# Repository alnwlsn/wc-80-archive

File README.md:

# The WC-80 (archive)

My homebrew Z80 computer which is not exactly a TRS-80 Model 1 clone. Archive from 2020-2023.

## Background
Some time ago when I was in college (not that long ago, mind you, it was like 2018), I found a TRS-80 Model 1. It was the first (non-IBM PC) retrocomputer I had ever got my hands on, and in my book, is absolutely legendary, for reasons I'll have to get into some other time. What's important is that what I got was *only* the keyboard, so no power supply, no cables, no display. The first thing I tried to do with it was cobble up a power supply, and wire up an adapter so I could plug the machine into a regular TV's composite video. I powered it on. It was a working unit. 

What you get with just the base Model 1 "keyboard" is:
- Z80 CPU @ 1.77 MHz
- ROM with Level II (microsoft) BASIC
- 16K of RAM
- video output
    - "almost" NTSC / RS170 (black and white only)
    - 64 columns x 16 rows, 6x12 px character resolution, fixed character set
- cassette interface
- the keyboard itself

That's  pretty limiting if you want to do stuff(tm) with the machine. In particular, the cassette interface is a real bottleneck, taking minutes on end to load things, and it's the only way to do so besides typing it in. People thought so too in the TRS-80's heyday, so the platform evolved to have floppy disks, more memory, various operating systems, a serial port, maybe even a hard drive. These were provided by a box that plugs into the TRS-80's keyboard called the 'Expansion Interface (EI)' I did not an Expansion Interface, and they were rare and expensive on Ebay. But, the TRS-80 is old enough that it is made mostly out of standard 74 logic ICs, rather than custom chips like the C64 or later machines have, and all the schematics are right there in the manual. Having more time than any other resource back then, I thought to myself "how hard can it be?"

Following the schematics, this is what led me to create my [hand-wired Expansion Interface unit](https://alnwlsn.com/projectrepository/index.php?title=TRS-80_Model_1_-_Wilson_Expansion_Interface) and had me boot my TRS-80 from a floppy disk for possibly the first time in its life. That was not quite built as stock though:
- SRAM for extra RAM instead of DRAMs
    - why not, RAM is cheap here in the future
    - 128K ram used, in 4 swappable banks of 32K
        - just because I can, haven't done much with this
- Arduino with 1K dual port RAM put in 'hole' in TRS-80 memory map at 0x3000
    - easy and quick way to get data from modern laptop to TRS-80 RAM
- 'equivalent' logic gates, not exact chips used in EI (based on what chips I happened to have or get easily)

The hand built unit had obvious problems though:
- tedious soldering assembly
- unreliable "stacked pin header" interconnects
- not very modular, hard to add more hardware
- fragile

I then started this project to clean up the hand built unit into some real PCBs, which would go into a backplane. If I wanted to add more hardware, I could just make another card. After building most of the EI, I realized that there wasn't all that much to the rest of the computer, so I built modules for that too. Thus, the WC-80 (W Cube Z80) was born.

It's a bit like a Model 1, with some Model III (more IO on the IO ports) and Model 4 (some peripherals like the video ram and keyboard can be moved around in the memory map, and there are multiple banks of memory). The main difference is that most of the hardware options are software controlled, so it needs to boot a rom that can initialize all the hardware, then load the TRS-80 ROMs and jump to the beginning of it.

As the system took shape, I thought I might install it into a case, and make a portable machine, but soon obtained a good number of real TRS-80 machines to work on instead. I haven't touched the WC-80 much since around 2022, which means I've forgotten most of whatever I was doing on it. Still, it's probably more useful published here as incomplete than just sitting on my hard drive. When I pick up this project again, I'll probably continue in a new repo, which will be linked here if it exists.

## General guidelines:
- 100x100mm typical board size
    - this is the cheap "loss leader" size offered by PCBWay and JLC. A board twice this area costs more than double the price.
- where possible, SMD SOIC packages
    - much more compact than DIP, but still easily solderable by hand with an iron
        - plus, you don't have to flip the board over
- 2 layer boards (cheapest)
- 0.2mm track width for data signals
    - fits between SOIC pads
- 74HCT (CMOS w/ TTL level inputs) over HC or LS parts, where possible
- autorouted (w/ some manual routing) with [TopoR](https://en.wikipedia.org/wiki/TopoR)
    - usually get my fill of manually routing boards at work
- designed around whatever ICs I can get for cheap
- fit as much stuff as I can onto each board
    - I paid for the whole board, I'm gonna use the whole board

## Boards
### Backplane

- 40-pin interconnect is derived from the 40-pin card edge on the back of the TRS-80 Model 1, though a few pins are different, so it can't be plugged in directly.
- 8 pin connectors on either side are for power and misc. signals.
- [next revision](boards/backplane2/new/) is just a straight interconnect, which is how it probably should be.
- [this version shown](boards/backplane/) has named nets, and the power rails and GNDs are connected together on the backplane.

### CPU board

- Z80 CPU
- memory map divided into 4x 16k slots, into which any 1 of 32 pages of RAM or 1 of any 32 pages of Flash ROM can be installed. 
    - bank selection by IO port
    - whole memory space is filled, but there is an INUSE pin on the backplane by which other boards can signal the CPU board that they want to use the memory space currently being accessed, in which case on-board memory will be disabled
- software selectable clock rate from 1.77MHz to 8MHz
    - CPU clock provided by a 16MHz clock feeding a counter chip which can count from 2 to 9. 16/9 happens to be pretty close to the 1.77MHz of the model 1. You also get more traditional clock rates of 2, 4 and 8Mhz.
- added the Model 1's cassette interface
    - can read and write TRS-80 Model 1 Level II tapes when running Level II ROMs
    - it can even load tapes played back at 4x speed in 8Mhz mode, seems to work just fine
    - includes reed relay for cassette remote switch
- battery backed RAM with integral RTC via [DS1315 Phantom Time chip](https://www.analog.com/en/products/ds1315.html)
    -   to get and set the RTC, you write a sequential series of special bytes to the RAM and the next byte written will come from the RTC
        - execution must be done either in a ROM or from external RAM, since you can't be both read the instructions and write the special sequence while being on the internal RAM
        - probably get rid of this in the next version, the Arduino board has the same thing already
- [I think this is the current version of the CPU](boards/cpu/cpu-rev2/)

### Keyboard

- key switches wired per TRS-80 key matrix
- NMI and Reset keys broken out on board
- some extra keys for which there is room on the matrix but normally no switch there (Control key, etc) have been added 
- memory mapped, but relocatable from the default 3800 address, like a model 4
    - only uses 256 addresses, not the minimally decoded 1K the Model 1 has
- 8 leds
- a fairly standard mechanical keyboard build otherwise
- keycaps are [custom labeled](keyboard-labels/) using the [lasered toner method](https://www.youtube.com/watch?v=_V5DmHmCMaU)
- this was supposed to be a simple PCB mounted switch design, but the switches I got ended up being plate mounted. I had to reconfigure my CNC machine to be a 3D printer, as I did not have one large enough to print a full-sized backplate at the time.

### Old CPU

- [despite being called 'cpu5' and the new one being 'cpu2', this is the older one](boards/cpu/cpu5/)
- same as the current CPU board, only using DIP chips and having a HP Dl1414 4-character LED display instead of the cassette interface. This display is usually not visible, so I got rid of it.

```alnwlsn-ssg
title: The WC-80 (archive)
subtitle: homebrew TRS-80 I made one time
date: 2025-07-16
labels: retrocomputing, trs80
```

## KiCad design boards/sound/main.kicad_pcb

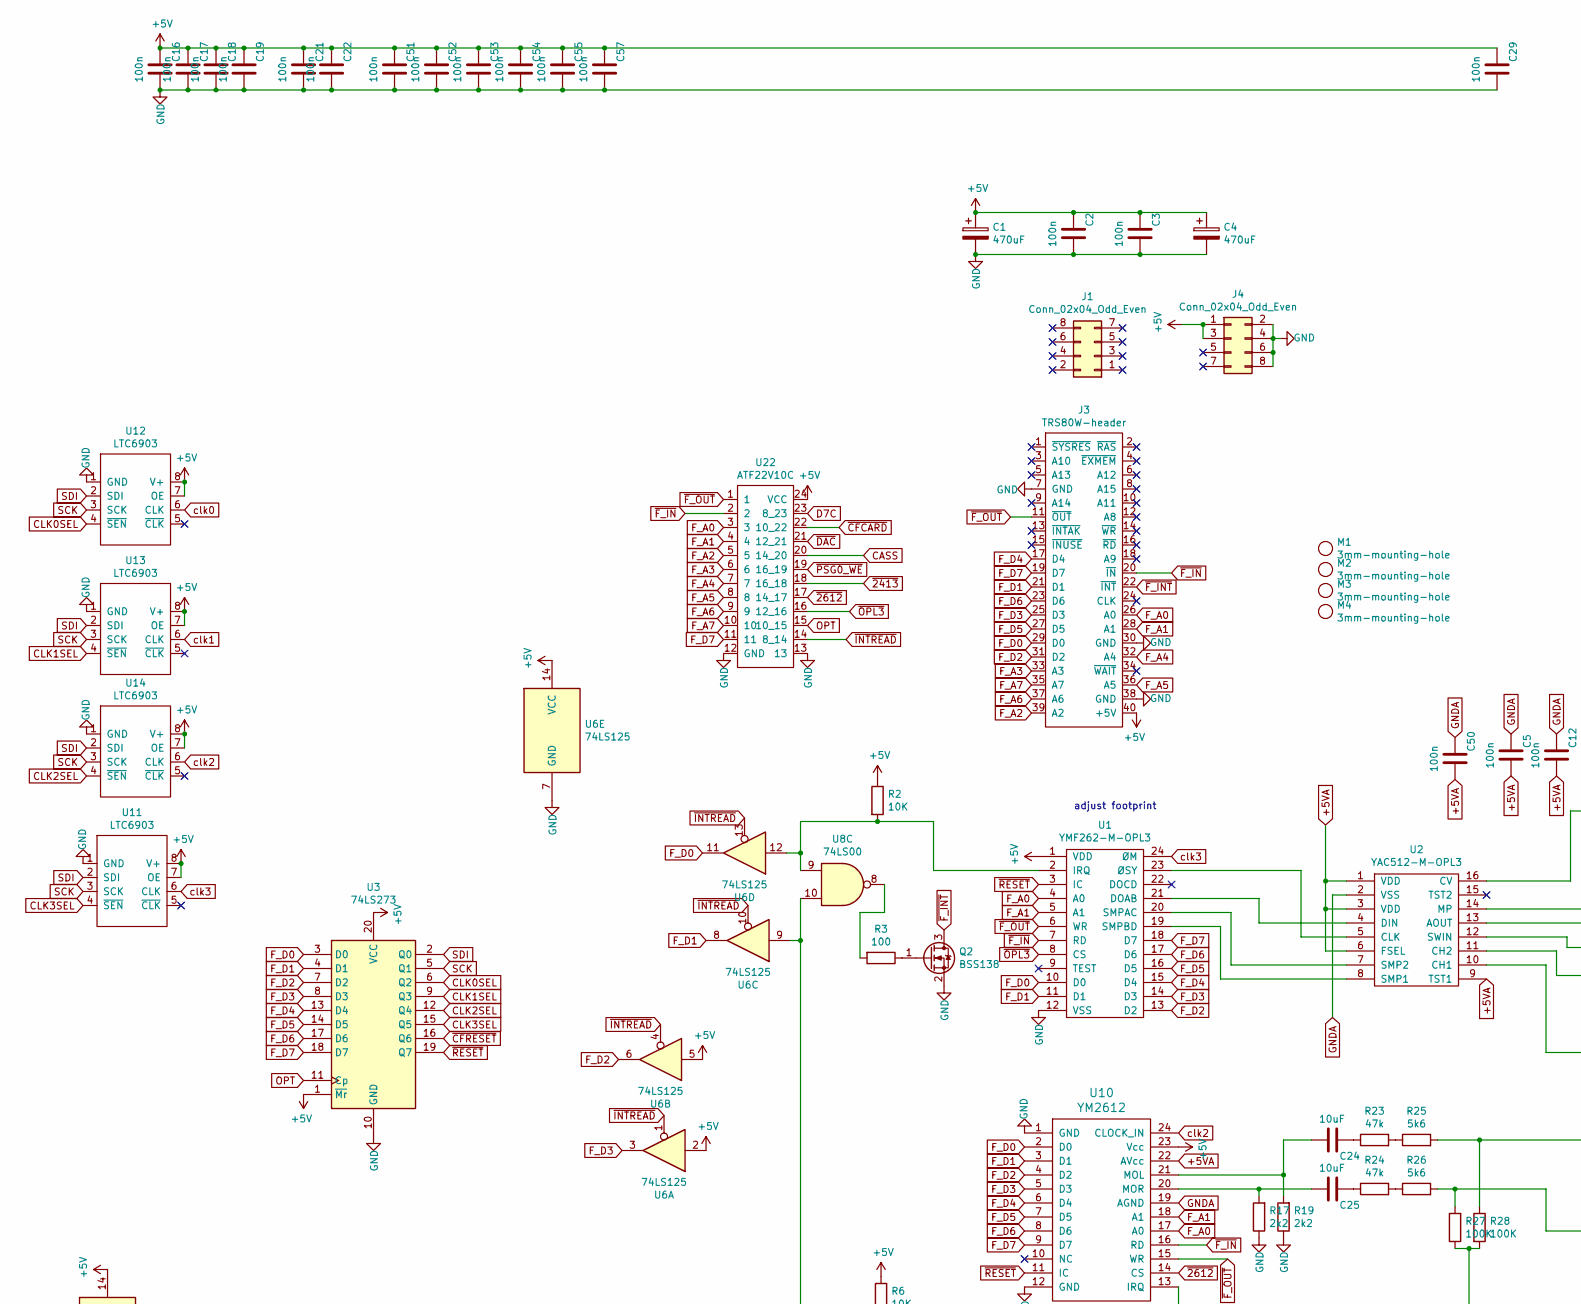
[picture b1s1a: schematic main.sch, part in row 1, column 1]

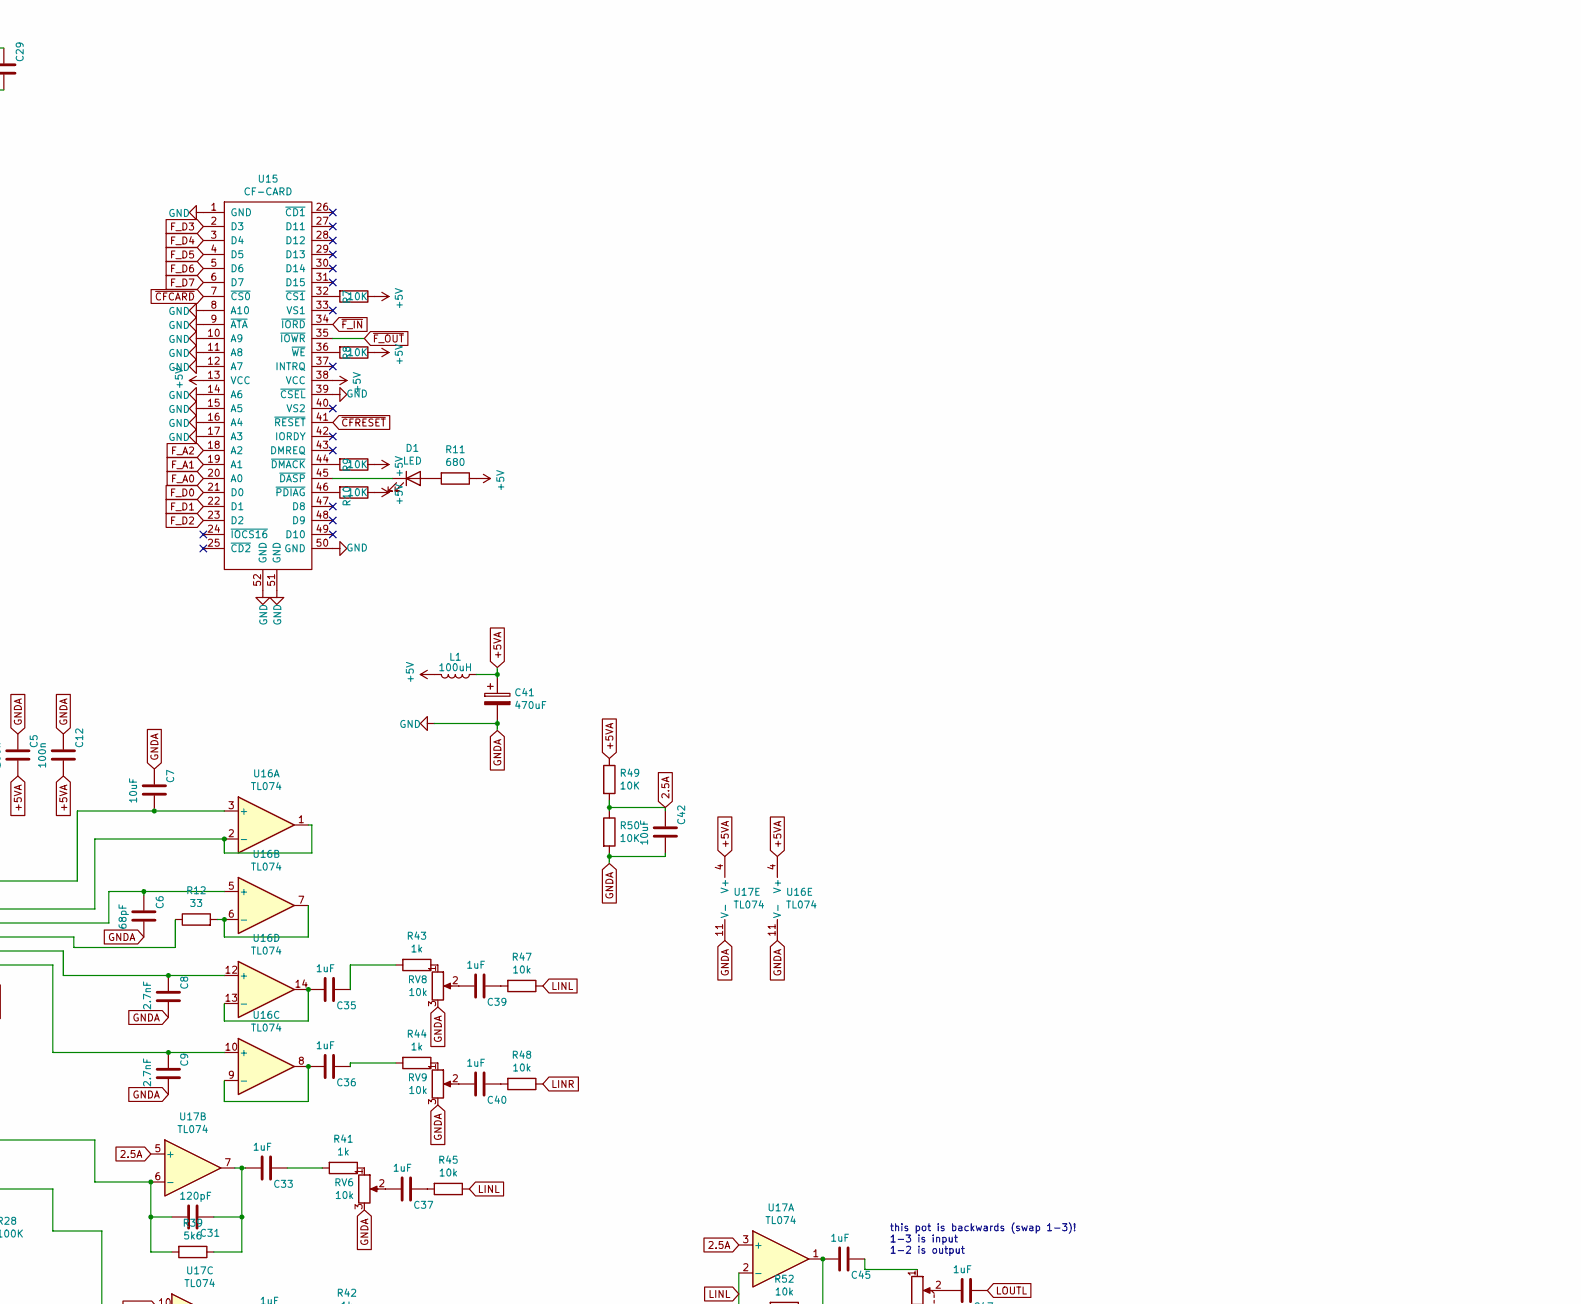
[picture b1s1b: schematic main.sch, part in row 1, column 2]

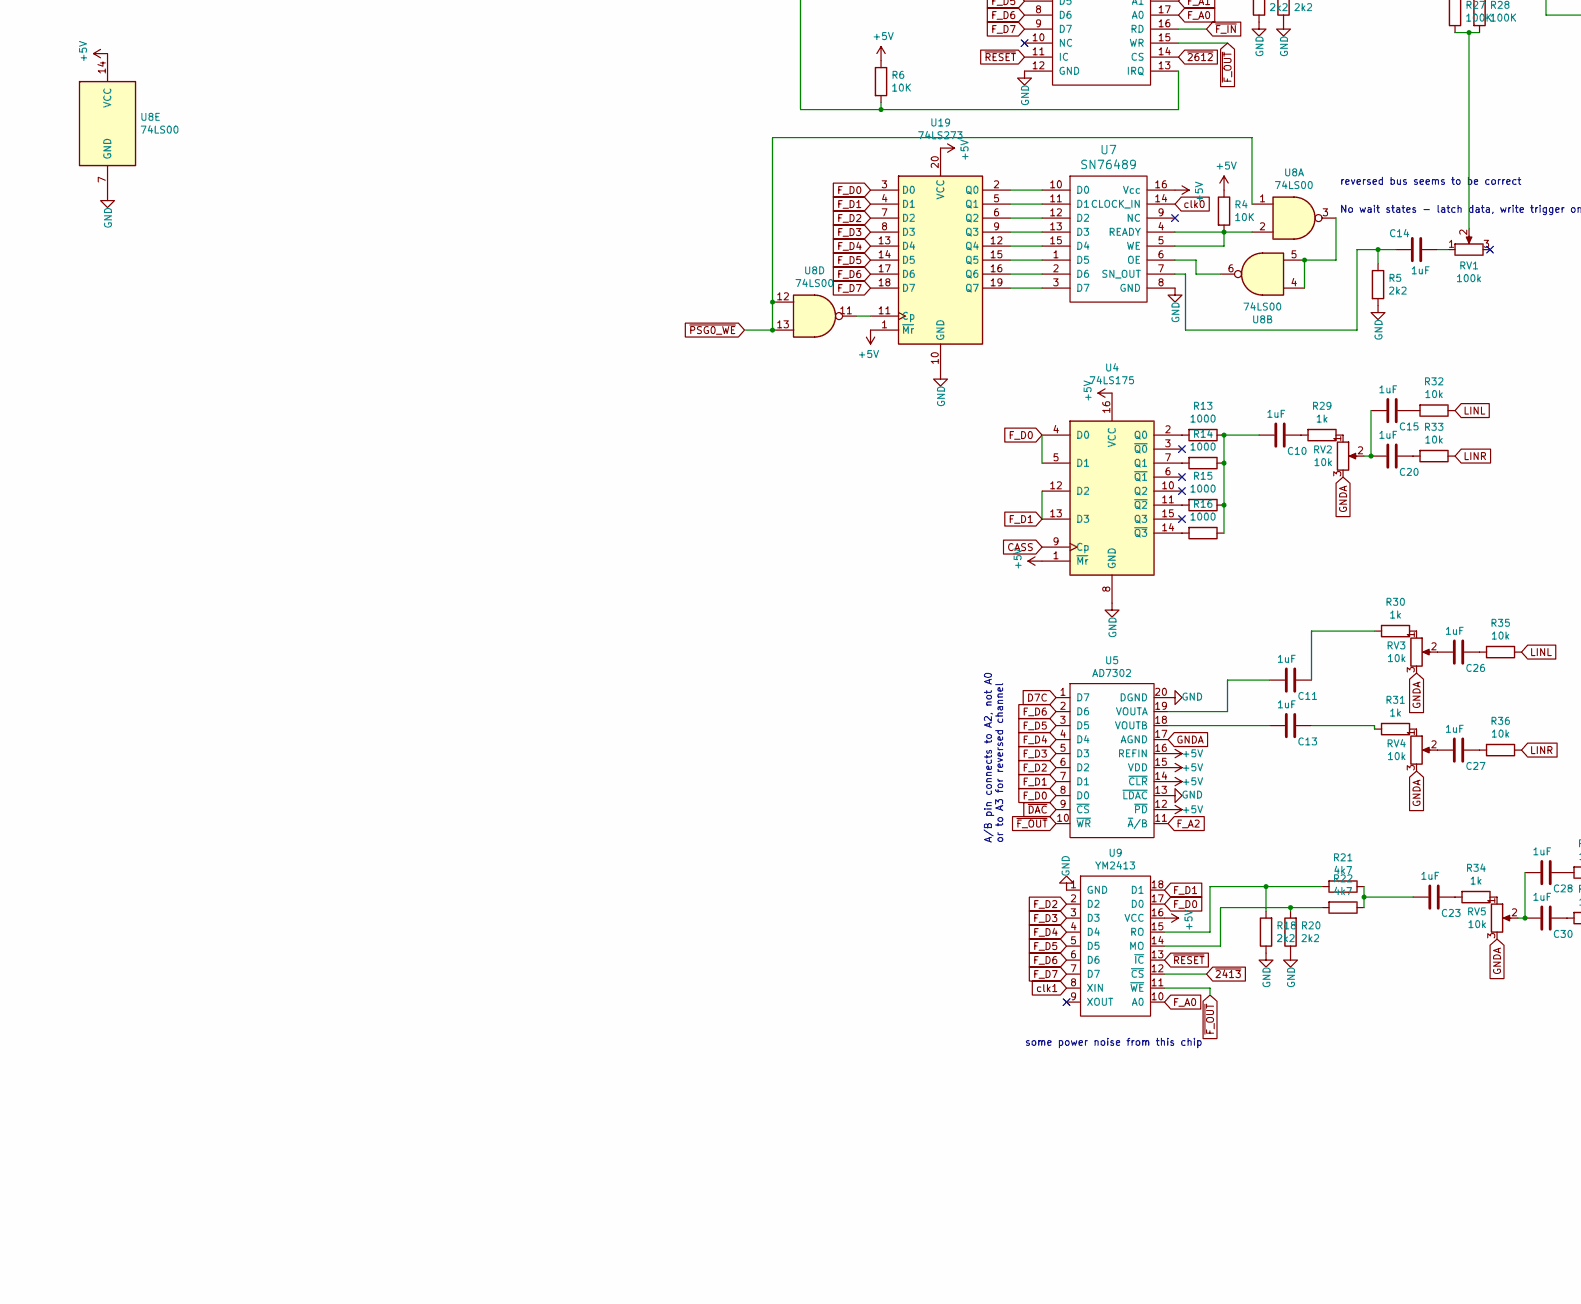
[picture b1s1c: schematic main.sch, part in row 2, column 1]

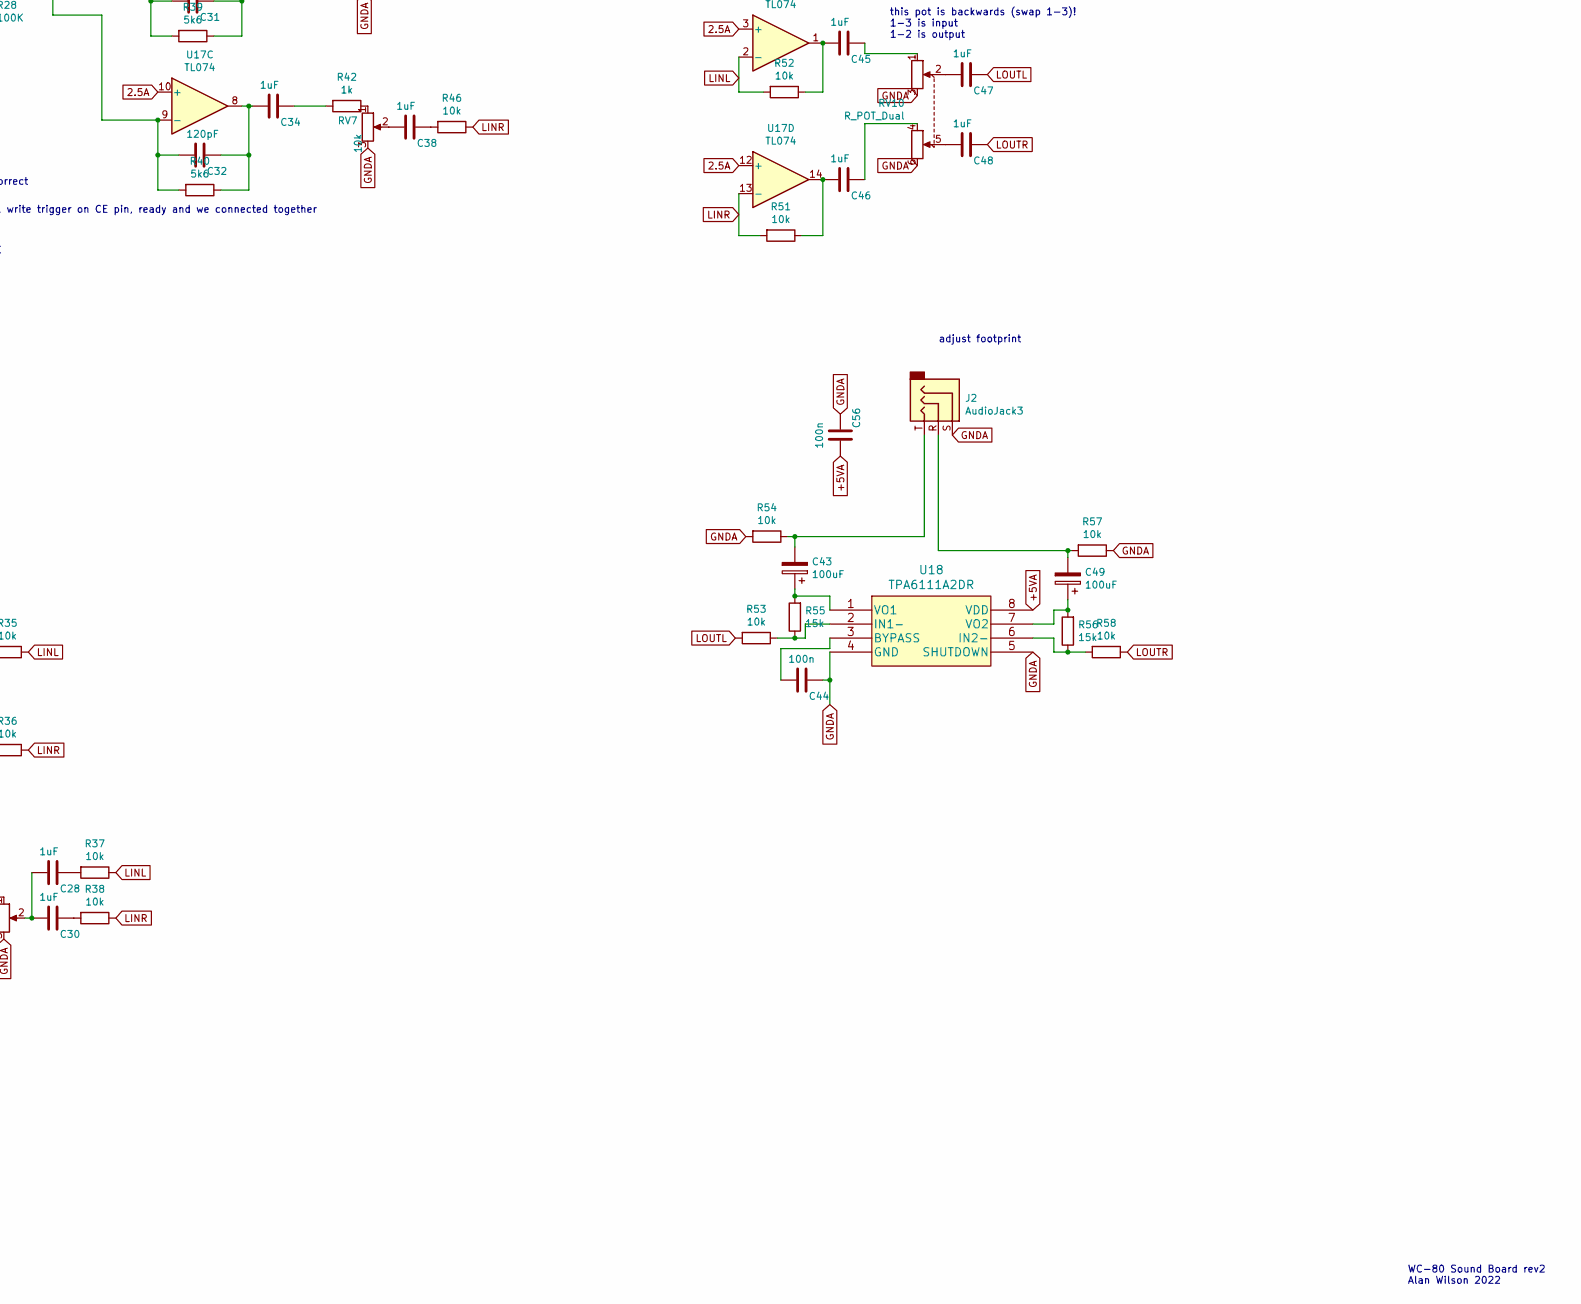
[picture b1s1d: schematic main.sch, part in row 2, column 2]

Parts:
C1, C4, C41: 470uF; CP_Radial_D8.0mm_P3.50mm
C2, C3, C5, C12, C16, C17, C18, C19, C21, C22, C29, C44, C50, C51, C52, C53, C54, C55, C56, C57: 100n; C_0805_2012Metric
C6: 68pF; C_0805_2012Metric
C7, C24, C25, C42: 10uF; C_0805_2012Metric
C8, C9: 2.7nF; C_0805_2012Metric
C10, C11, C13, C14, C15, C20, C23, C26, C27, C28, C30, C33, C34, C35, C36, C37, C38, C39, C40, C45, C46, C47, C48: 1uF; C_0805_2012Metric
C31, C32: 120pF; C_0805_2012Metric
C43, C49: 100uF; CP_Elec_6.3x5.4
D1: LED; LED_D3.0mm
J1, J4: Conn_02x04_Odd_Even; PinHeader_2x04_P2.54mm_Vertical
J2: AudioJack3; SWITCHCRAFT_35RAPC4BHN2
J3: TRS80W-header; PinHeader_2x20_P2.54mm_Vertical
L1: 100uH; SWPA5040S
M1, M2, M3, M4: 3mm-mounting-hole; MountingHole_3.2mm_M3_DIN965
Q2: BSS138; SOT-23
R2, R4, R6, R7, R8, R9, R10, R49, R50: 10K; R_0805_2012Metric
R3: 100; R_0805_2012Metric
R5, R17, R18, R19, R20: 2k2; R_0805_2012Metric
R11: 680; R_0805_2012Metric
R12: 33; R_0805_2012Metric
R13, R14, R15, R16: 1000; R_0805_2012Metric
R21, R22: 4k7; R_0805_2012Metric
R23, R24: 47k; R_0805_2012Metric
R25, R26, R39, R40: 5k6; R_0805_2012Metric
R27, R28: 100K; R_0805_2012Metric
R29, R30, R31, R34, R41, R42, R43, R44: 1k; R_0805_2012Metric
R32, R33, R35, R36, R37, R38, R45, R46, R47, R48, R51, R52, R53, R54, R57, R58: 10k; R_0805_2012Metric
R55, R56: 15k; R_0805_2012Metric
RV1: 100k; 3362P-1-103LF
RV2, RV3, RV4, RV5, RV6, RV7, RV8, RV9: 10k; 3362P-1-103LF
RV10: R_POT_Dual; Potentiometer_Alps_RK097_Dual_Horizontal
U1: YMF262-M-OPL3; SOIC-24W_7.5x15.4mm_P1.27mm
U2: YAC512-M-OPL3; SOIC-16W_5.3x10.2mm_P1.27mm
U3, U19: 74LS273; SO-20_5.3x12.6mm_P1.27mm
U4: 74LS175; SOIC-16_3.9x9.9mm_P1.27mm
U5: AD7302; SOIC-20W_7.5x12.8mm_P1.27mm
U6: 74LS125; SOIC-14_3.9x8.7mm_P1.27mm
U7: SN76489; DIP-16_W7.62mm_Socket
U8: 74LS00; SOIC-14_3.9x8.7mm_P1.27mm
U9: YM2413; DIP-18_W7.62mm_Socket
U10: YM2612; DIP-24_W15.24mm_Socket
U11, U12, U13, U14: LTC6903; MSOP-8_3x3mm_P0.65mm
U15: CF-CARD; UMAX CFH-L3C1LBL01MN0
U16: TL074
U17: TL074; SOIC-14_3.9x8.7mm_P1.27mm
U18: TPA6111A2DR; SOIC-8_3.9x4.9mm_P1.27mm
U22: ATF22V10C; DIP-24_W7.62mm_Socket

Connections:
2.5A: C42.1, R49.2, R50.1, U17.3 (+), U17.5 (+), U17.10 (+), U17.12 (+)
+5V: C1.1, C2.1, C3.1, C4.1, C16.1, C17.1, C18.1, C19.1, C21.1, C22.1, C29.1, C51.1, C52.1, C53.1, C54.1, C55.1, C57.1, J3.40 (+5V), J4.1, J4.3, L1.2, R2.1, R4.1, R6.1, R7.1, R8.1, R9.1, R10.1, R11.1, U1.1 (VDD), U3.1 (~Mr), U3.20 (VCC), U4.1 (~Mr), U4.16 (VCC), U5.12 (~PD~), U5.14 (~CLR~), U5.15 (VDD), U5.16 (REFIN), U6.2, U6.5, U6.14 (VCC), U7.16 (Vcc), U8.14 (VCC), U9.16 (VCC), U10.23 (Vcc), U11.7 (OE), U11.8 (V+), U12.7 (OE), U12.8 (V+), U13.7 (OE), U13.8 (V+), U14.7 (OE), U14.8 (V+), U15.13 (VCC), U15.38 (VCC), U19.1 (~Mr), U19.20 (VCC), U22.24 (VCC)
+5VA: C5.2, C12.2, C41.1, C50.2, C56.2, L1.1, R49.1, U2.1 (VDD), U2.3 (VDD), U2.6 (FSEL), U2.9 (TST1), U10.22 (AVcc), U16.4 (V+), U17.4 (V+), U18.8 (VDD)
CASS: U4.9 (Cp), U22.20 (14_20)
CLK0SEL: U3.6 (Q2), U12.4 (~SEN~)
CLK1SEL: U3.9 (Q3), U13.4 (~SEN~)
CLK2SEL: U3.12 (Q4), U14.4 (~SEN~)
CLK3SEL: U3.15 (Q5), U11.4 (~SEN~)
D7C: U5.1 (D7), U22.23 (8_23)
F_A1: J3.28 (A1), U1.5 (A1), U10.18 (A1), U15.19 (A1), U22.4
F_A3: J3.33 (A3), U22.6
F_A4: J3.32 (A4), U22.7
F_A5: J3.36 (A5), U22.8
F_A6: J3.37 (A6), U22.9
F_A7: J3.35 (A7), U22.10
F_D0: J3.29 (D0), U1.10 (D0), U3.3 (D0), U4.4 (D0), U4.5 (D1), U5.8 (D0), U6.11, U7.10 (D0), U9.17 (D0), U10.2 (D0), U15.21 (D0), U19.2 (Q0), U19.3 (D0)
F_D1: J3.21 (D1), U1.11 (D1), U3.4 (D1), U4.12 (D2), U4.13 (D3), U5.7 (D1), U6.8, U7.11 (D1), U9.18 (D1), U10.3 (D1), U15.22 (D1), U19.4 (D1), U19.5 (Q1)
F_D2: J3.31 (D2), U1.13 (D2), U3.7 (D2), U5.6 (D2), U6.6, U7.12 (D2), U9.2 (D2), U10.4 (D2), U15.23 (D2), U19.6 (Q2), U19.7 (D2)
F_D3: J3.25 (D3), U1.14 (D3), U3.8 (D3), U5.5 (D3), U6.3, U7.13 (D3), U9.3 (D3), U10.5 (D3), U15.2 (D3), U19.8 (D3), U19.9 (Q3)
F_D4: J3.17 (D4), U1.15 (D4), U3.13 (D4), U5.4 (D4), U7.15 (D4), U9.4 (D4), U10.6 (D4), U15.3 (D4), U19.12 (Q4), U19.13 (D4)
F_D5: J3.27 (D5), U1.16 (D5), U3.14 (D5), U5.3 (D5), U7.1 (D5), U9.5 (D5), U10.7 (D5), U15.4 (D5), U19.14 (D5), U19.15 (Q5)
F_D6: J3.23 (D6), U1.17 (D6), U3.17 (D6), U5.2 (D6), U7.2 (D6), U9.6 (D6), U10.8 (D6), U15.5 (D6), U19.16 (Q6), U19.17 (D6)
F_D7: J3.19 (D7), U1.18 (D7), U3.18 (D7), U7.3 (D7), U9.7 (D7), U10.9 (D7), U15.6 (D7), U19.18 (D7), U19.19 (Q7), U22.11
F_WAIT: J3.34 (~WAIT~); also elsewhere on the board
LINL: R32.1, R35.1, R37.1, R45.1, R47.1, R52.2, U17.2 (-)
LINR: R33.1, R36.1, R38.1, R46.1, R48.1, R51.2, U17.13 (-)
LOUTL: C47.1, R53.2
LOUTR: C48.1, R58.1
unnamed: C6.1, U2.13 (AOUT), U16.5 (+)
unnamed: C7.2, U2.16 (CV), U16.3 (+)
unnamed: C8.1, U2.11 (CH2), U16.12 (+)
unnamed: C9.1, U2.10 (CH1), U16.10 (+)
unnamed: C10.1, R29.2
unnamed: C10.2, R13.1, R14.1, R15.1, R16.1
unnamed: C11.1, R30.2
unnamed: C11.2, U5.19 (VOUTA)
unnamed: C13.1, R31.2
unnamed: C13.2, U5.18 (VOUTB)
unnamed: C14.1, R5.1, U7.7 (SN_OUT)
unnamed: C14.2, RV1.1
unnamed: C15.1, R32.2
unnamed: C15.2, C20.2, RV2.2
unnamed: C20.1, R33.2
unnamed: C23.1, R34.2
unnamed: C23.2, R21.1, R22.1
unnamed: C24.1, R23.1
unnamed: C24.2, R19.2, U10.21 (MOL)
unnamed: C25.1, R24.1
unnamed: C25.2, R17.2, U10.20 (MOR)
unnamed: C26.1, R35.2
unnamed: C26.2, RV3.2
unnamed: C27.1, R36.2
unnamed: C27.2, RV4.2
unnamed: C28.1, R37.2
unnamed: C28.2, C30.2, RV5.2
unnamed: C30.1, R38.2
unnamed: C31.1, C33.2, R39.1, U17.7
unnamed: C31.2, R25.2, R28.1, R39.2, U17.6 (-)
unnamed: C32.1, C34.2, R40.1, U17.8
unnamed: C32.2, R26.2, R27.2, R40.2, U17.9 (-)
unnamed: C33.1, R41.2
unnamed: C34.1, R42.2
unnamed: C35.1, R43.2
unnamed: C35.2, U16.13 (-), U16.14
unnamed: C36.1, R44.2
unnamed: C36.2, U16.8, U16.9 (-)
unnamed: C37.1, R45.2
unnamed: C37.2, RV6.2
unnamed: C38.1, R46.2
unnamed: C38.2, RV7.2
unnamed: C39.1, R47.2
unnamed: C39.2, RV8.2
unnamed: C40.1, R48.2
unnamed: C40.2, RV9.2
unnamed: C43.1, R55.2, U18.1 (VO1)
unnamed: C43.2, J2.T, R54.1
unnamed: C44.2, U18.3 (BYPASS)
unnamed: C45.1, RV10.1
unnamed: C45.2, R52.1, U17.1
unnamed: C46.1, RV10.4
unnamed: C46.2, R51.1, U17.14
unnamed: C47.2, RV10.2
unnamed: C48.2, RV10.5
unnamed: C49.1, R56.2, U18.7 (VO2)
unnamed: C49.2, J2.R, R57.2
unnamed: D1.1 (K), U15.45 (~DASP~)
unnamed: D1.2 (A), R11.2
unnamed: Q2.1 (G), R3.1
unnamed 115: U8.11, U19.11 (Cp); also elsewhere on the board
unnamed: R2.2, U1.2 (IRQ), U6.12, U8.9
unnamed: R3.2, U8.8
unnamed: R6.2, U6.9, U8.10, U10.13 (IRQ)
unnamed: R7.2, U15.32 (~CS1~)
unnamed: R8.2, U15.36 (~WE~)
unnamed: R9.2, U15.44 (~DMACK~)
unnamed: R10.2, U15.46 (~PDIAG~)
unnamed: R12.1, U2.12 (SWIN)
unnamed: R12.2, U16.6 (-), U16.7
unnamed: R13.2, U4.2 (Q0)
unnamed: R14.2, U4.7 (Q1)
unnamed: R15.2, U4.11 (~Q2)
unnamed: R16.2, U4.14 (~Q3)
unnamed: R18.2, R21.2, U9.15 (RO)
unnamed: R20.2, R22.2, U9.14 (MO)
unnamed: R23.2, R25.1
unnamed: R24.2, R26.1
unnamed: R27.1, R28.2, RV1.2
unnamed: R29.1, RV2.1
unnamed: R30.1, RV3.1
unnamed: R31.1, RV4.1
unnamed: R34.1, RV5.1
unnamed: R41.1, RV6.1
unnamed: R42.1, RV7.1
unnamed: R43.1, RV8.1
unnamed: R44.1, RV9.1
unnamed: R53.1, R55.1, U18.2 (IN1-)
unnamed: R56.1, R58.2, U18.6 (IN2-)
unnamed: U1.19 (SMPBD), U2.8 (SMP1)
unnamed: U1.20 (SMPAC), U2.7 (SMP2)
unnamed: U1.21 (DOAB), U2.4 (DIN)
unnamed: U1.23 (ØSY), U2.5 (CLK)
unnamed: U2.14 (MP), U16.1, U16.2 (-)
OPT: U3.11 (Cp), U22.15 (10_15)
SCK: U3.5 (Q1), U11.3 (SCK), U12.3 (SCK), U13.3 (SCK), U14.3 (SCK)
SDI: U3.2 (Q0), U11.2 (SDI), U12.2 (SDI), U13.2 (SDI), U14.2 (SDI)
clk0: U7.14 (CLOCK_IN), U12.6 (CLK)
clk1: U9.8 (XIN), U13.6 (CLK)
clk2: U10.24 (CLOCK_IN), U14.6 (CLK)
clk3: U1.24 (ØM), U11.6 (CLK)
~2413~: U9.12 (~CS~), U22.18 (16_18)
~2612~: U10.14 (CS), U22.17 (14_17)
~CFCARD~: U15.7 (~CS0~), U22.22 (10_22)
~CFRESET~: U3.16 (Q6), U15.41 (~RESET~)
~DAC~: U5.9 (~CS~), U22.21 (12_21)
~F_INT~: J3.22 (~INT~), Q2.3 (D)
~F_IN~: J3.20 (~IN~), U1.7 (RD), U10.16 (RD), U15.34 (~IORD~), U22.2
~F_OUT~: J3.11 (~OUT~), U1.6 (WR), U5.10 (~WR~), U9.11 (~WE~), U10.15 (WR), U15.35 (~IOWR~), U22.1
~INTREAD~: U6.1, U6.4, U6.10, U6.13, U22.14 (8_14)
~OPL3~: U1.8 (CS), U22.16 (12_16)
~RESET~: U1.3 (IC), U3.19 (Q7), U9.13 (~IC~), U10.11 (IC)

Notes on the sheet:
WC-80 Sound Board rev2 Alan Wilson 2022
adjust footprint
A/B pin connects to A2, not A0 or to A3 for reversed channel
this pot is backwards (swap 1-3)! 1-3 is input 1-2 is output
reversed bus seems to be correct
No wait states - latch data, write trigger on CE pin, ready and we connected together
some power noise from this chip

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
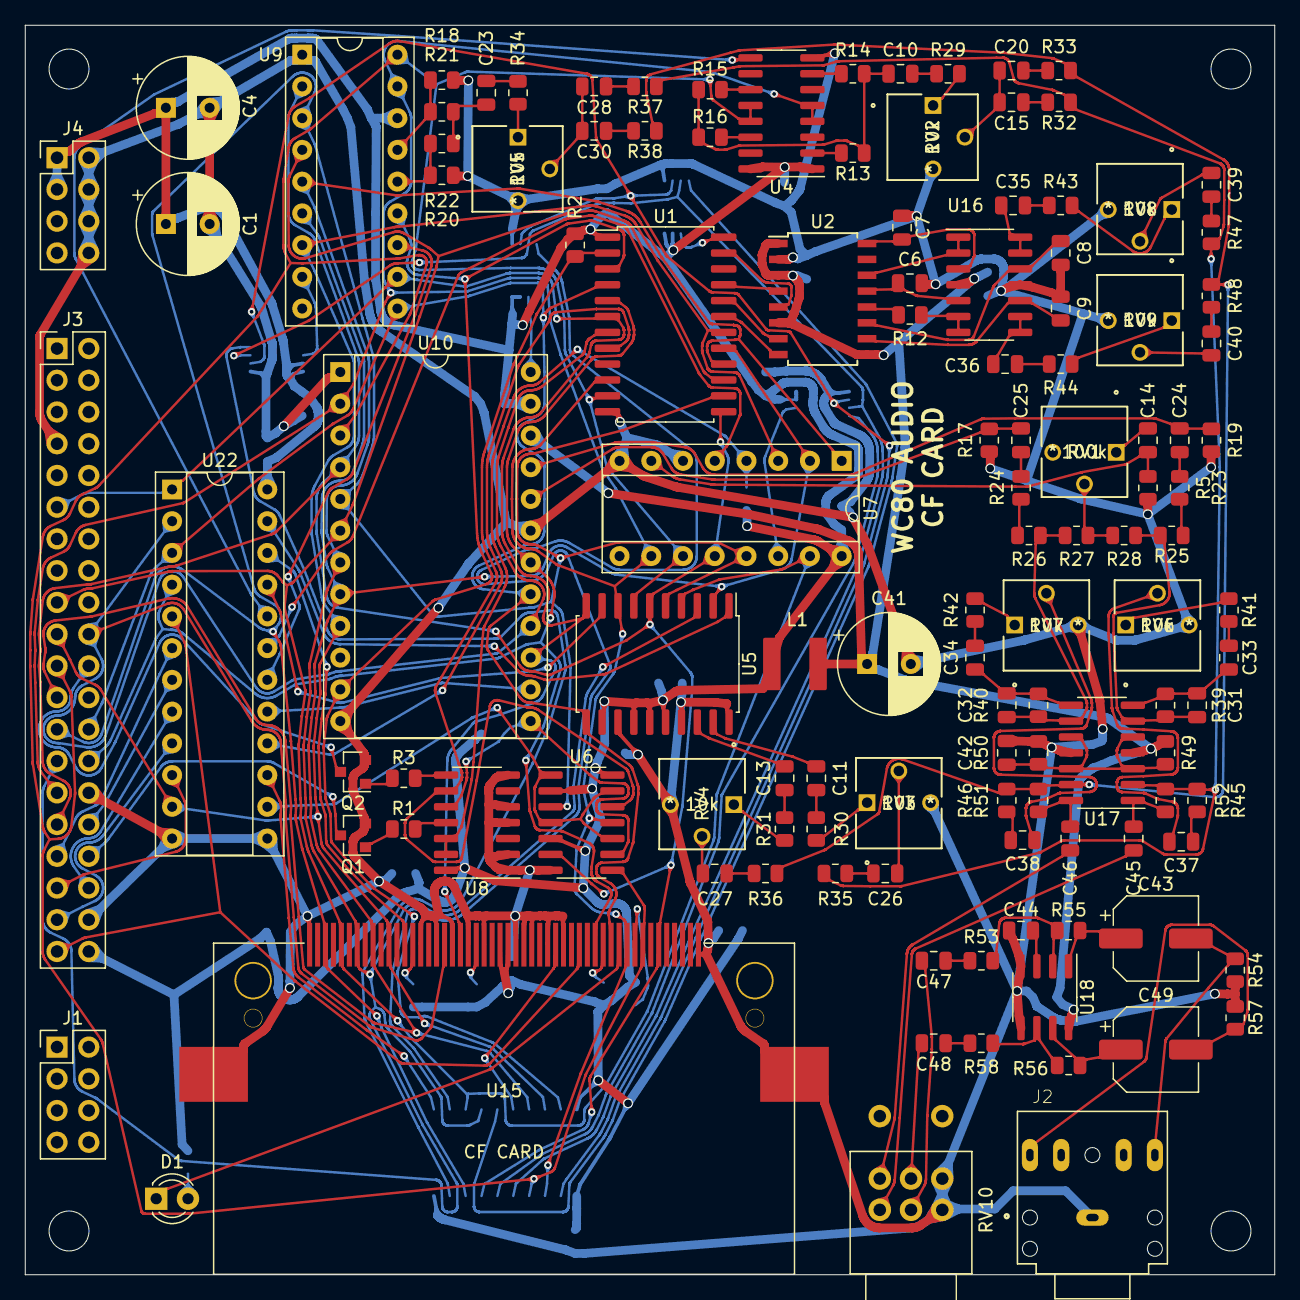
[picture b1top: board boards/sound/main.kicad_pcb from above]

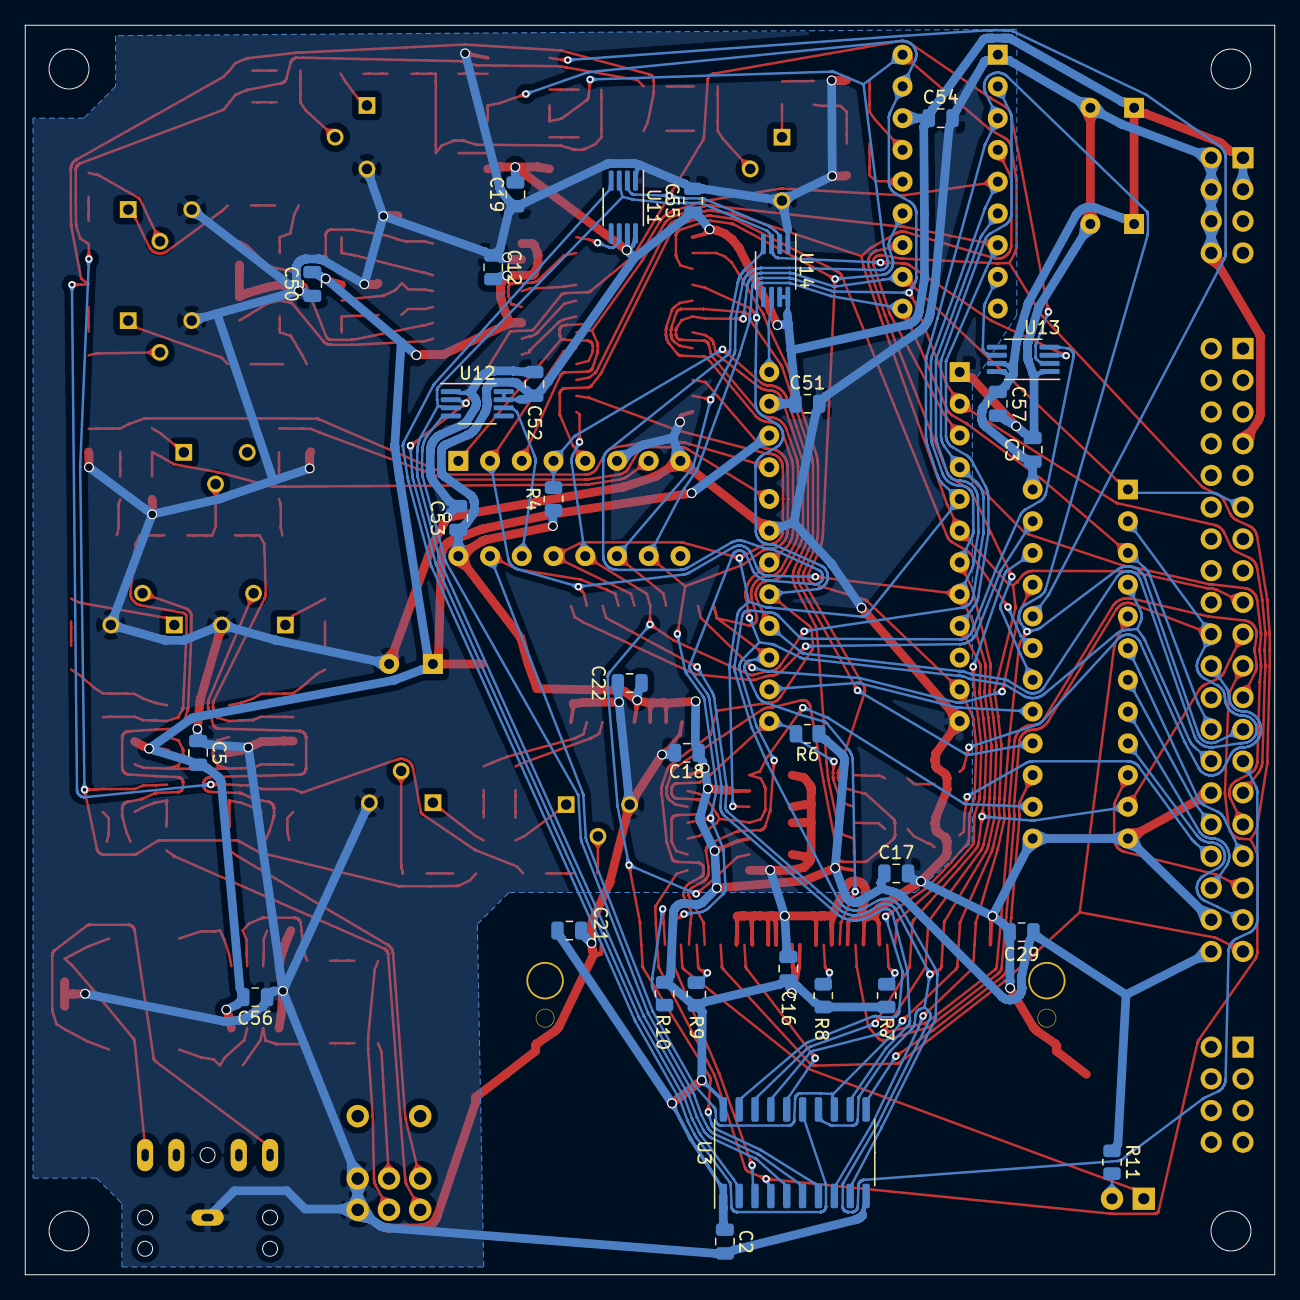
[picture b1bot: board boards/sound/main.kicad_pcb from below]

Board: 2 copper layers, 100.0 x 100.0 mm, 156 parts (31 on the bottom side), 146 nets.

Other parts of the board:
Q1: BSS138; SOT-23
R1: 100; R_0805_2012Metric

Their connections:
F_WAIT: Q1.3; also elsewhere on the board
unnamed: Q1.1, R1.1
unnamed 115: R1.2; also elsewhere on the board

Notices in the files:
parts and their libraries:
Copyright 2016 Accelerated Designs. All rights reserved.
